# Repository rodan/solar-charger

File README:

12v lead-acid battery charger for 15-36V photovoltaic cells

 UNDER DEVELOPMENT

 source:       https://github.com/rodan/solar-charger 
 author:       Petre Rodan <2b4eda@subdimension.ro>
 license:      GNU GPLv3
 toolchain used: msp430-elf-gcc (Mitto Systems Limited - msp430-gcc 9.2.0.50) 9.2.0 linux

Features:
 - an MSP430F5510 uC controls all aspects of charging a 12v Pb battery
 - programming either via spy-bi-wire or usb (untested)
 - logging capability to a uSd card
 - backup 3v Li cell for keeping the RTC up-to-date
 - analog readout of battery voltage, input voltage, charge current, thermistor temperature, internal temperature
 - possibility to stop the charge if a condition is met
 - 8 status leds for verbose blinkiness
 - very low quiescent current

rev1 - used a LandStar charge controller that got replaced in rev3 with a PB137ACV ic
rev3 - 3V Li cell acts as bakup power for the uC, an SDcard is provided for logging
rev4 - SDcard is removed, 3V Li cell replaced by a 3.7v lipo + charging circuitry

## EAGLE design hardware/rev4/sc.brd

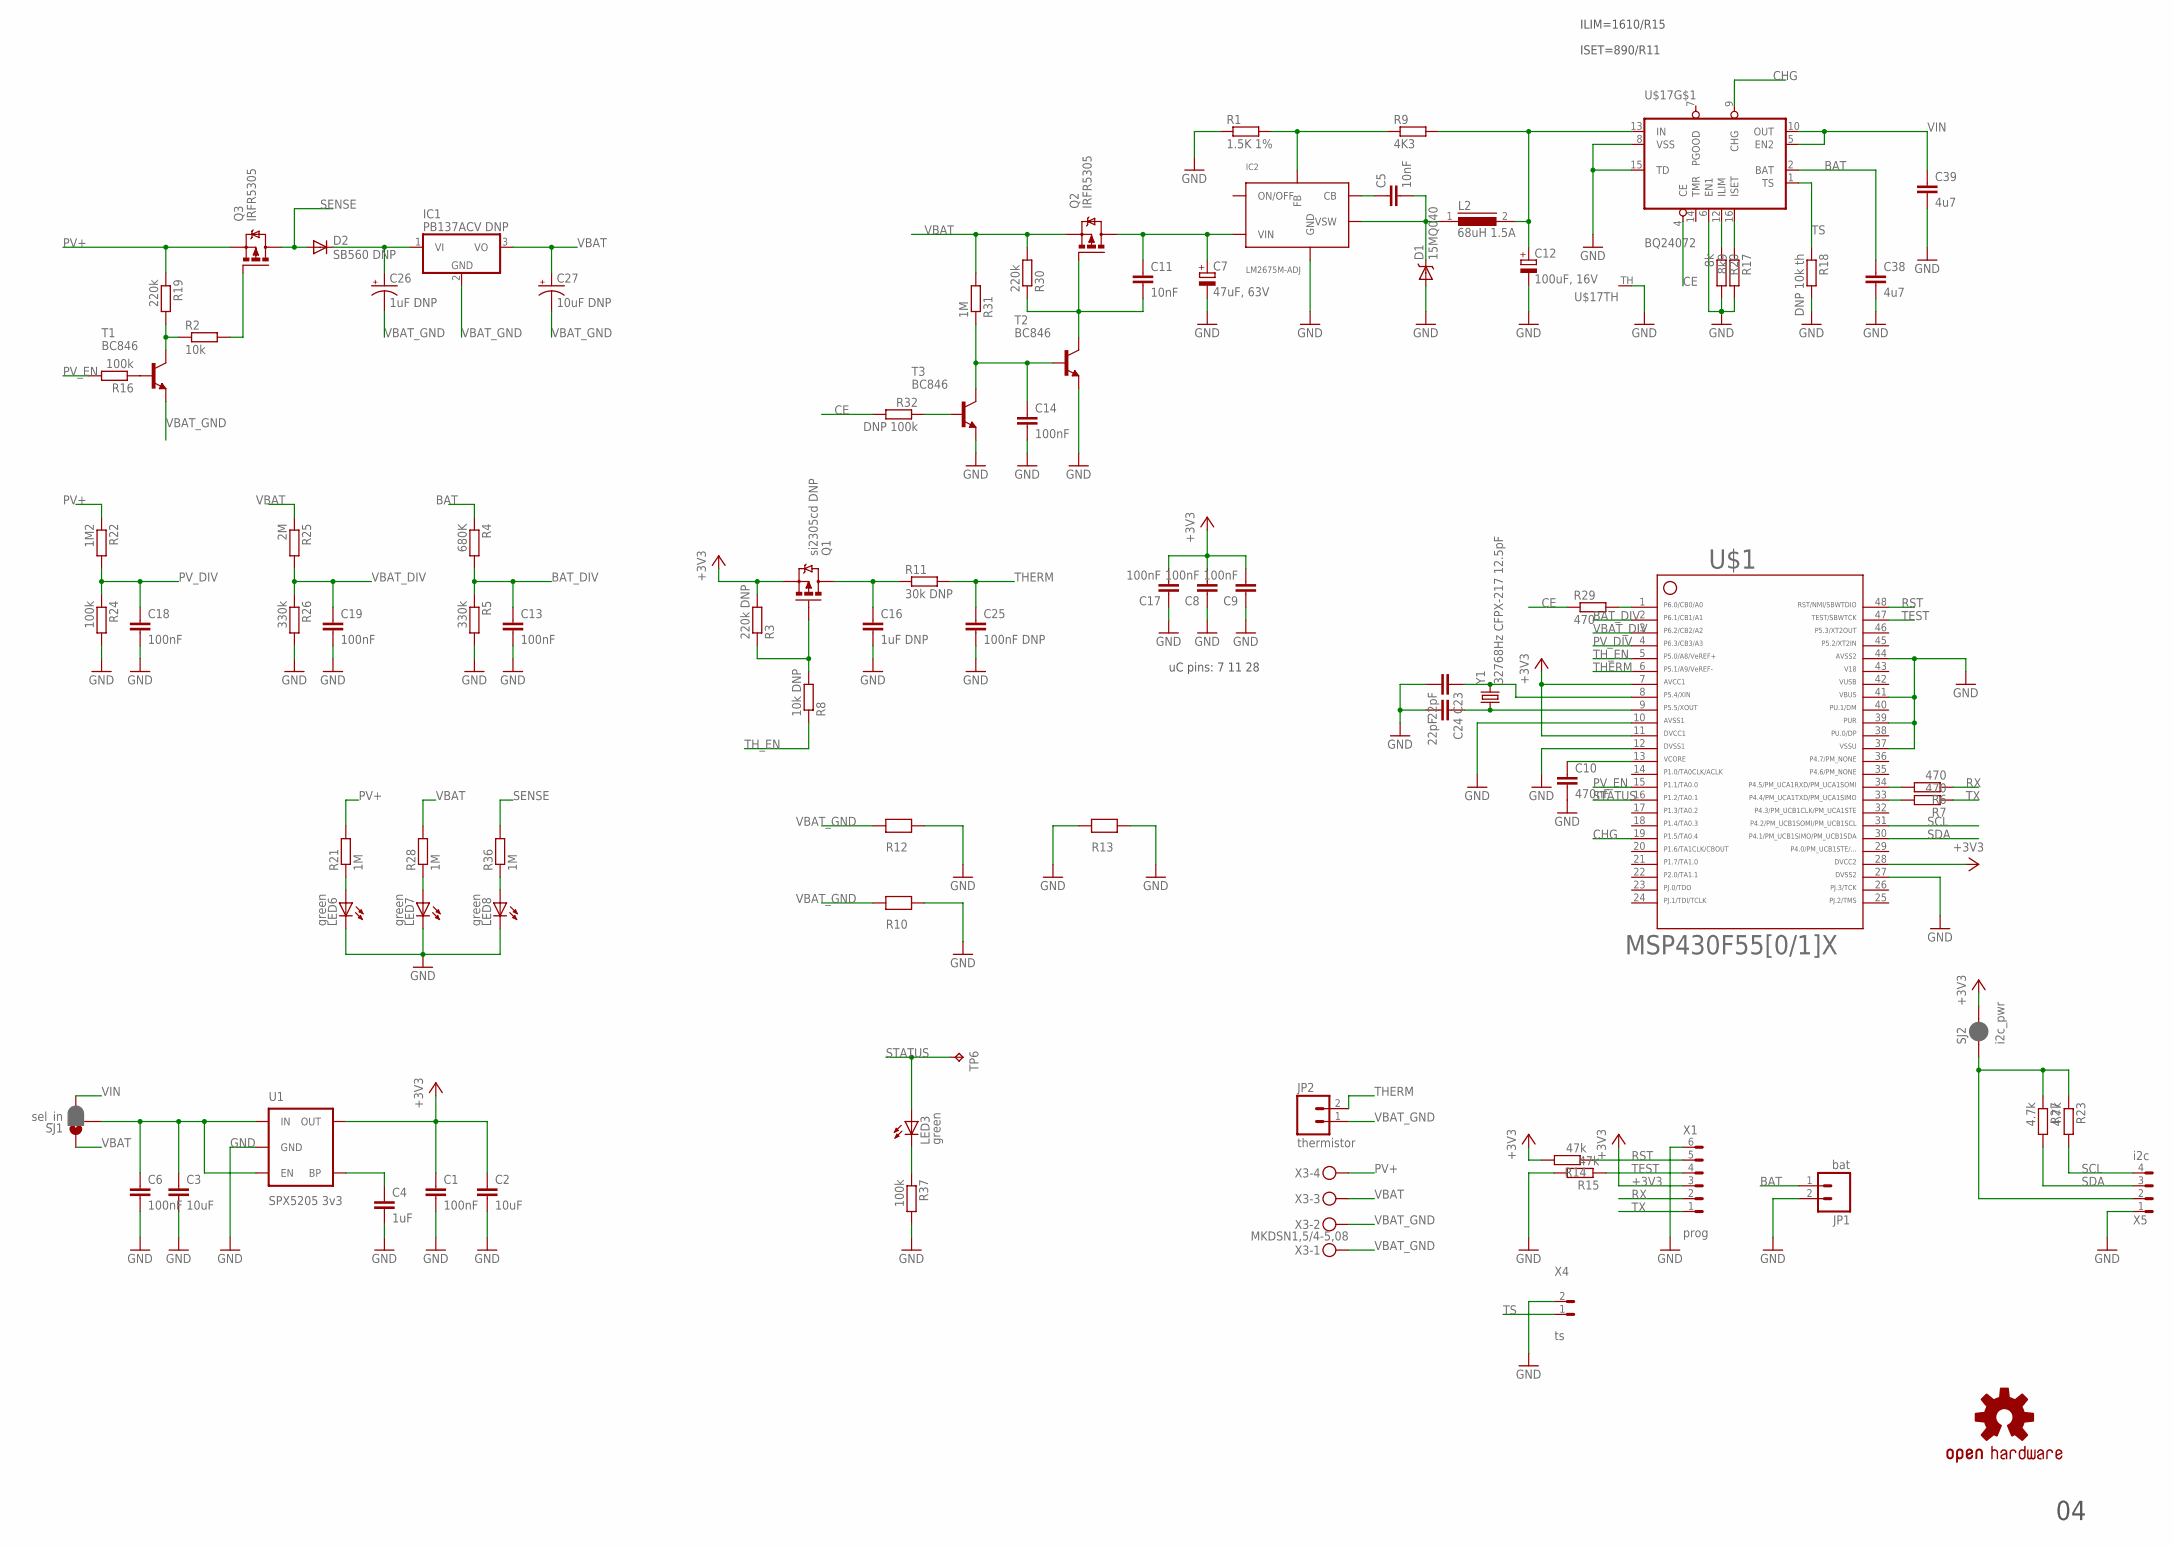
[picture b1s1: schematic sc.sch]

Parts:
C1, C6, C8, C9, C13, C14, C17, C18, C19: 100nF; C0805
C2, C3: 10uF; C1206
C4: 1uF; C0805
C5, C11: 10nF; C0805
C7: 47uF, 63V; PANASONIC_F
C10: 470nF; C0805
C12: 100uF, 16V; PANASONIC_D
C16: 1uF DNP; C0805
C23, C24: 22pF; C0805
C25: 100nF DNP; C0805
C26: 1uF DNP; PANASONIC_D
C27: 10uF DNP; PANASONIC_D
C38, C39: 4u7; C1206
D1: 15MQ040; SMA-DIODE
D2: SB560 DNP; C1702-05
IC1: PB137ACV DNP; TO220V
IC2: LM2675M-ADJ; SO-08
JP1: bat; 1X02
JP2: thermistor; 1X02
L2: 68uH 1.5A; DR125
LED3: green; CHIPLED_0805
LED6, LED7, LED8: green; CHIP-LED0805
Q1: si2305cd DNP; SOT23-3_POWER@1
Q2, Q3: IRFR5305; D-PAK_TO252AA
R1: 1.5K 1%; R0805W
R2: 10k; R0805W
R3: 220k DNP; R0805W
R4: 680K; R0805W
R5, R26: 330k; R0805W
R6, R7, R29: 470; R0805W
R8: 10k DNP; R0805W
R9: 4K3; R0805W
R10, R12, R13: 0R_0805; R0805W
R11: 30k DNP; R0805W
R14, R15: 47k; R0805W
R16, R24, R37: 100k; R0805W
R17: 8k9; R0805W
R18: DNP 10k th; R0805W
R19, R30: 220k; R0805W
R20: 8k; R0805W
R21, R28, R31, R36: 1M; R0805W
R22: 1M2; R0805W
R23, R27: 4.7k; R0805W
R25: 2M; R0805W
R32: DNP 100k; R0805W
SJ1: sel_in; PAD-JUMPER-3-2OF3_NC_BY_PASTE_YES_SILK_FULL_BOX
SJ2: i2c_pwr; PAD-JUMPER-2-NC_BY_PASTE_YES_SILK
T1, T2, T3: BC846; SOT23
TP6: TPTP12R; TP12R
U1: SPX5205 3v3; SOT23-5
U$1: F55[0/1]X---PT48; PT48
U$7: OSHW-LOGOM; OSHW-LOGO-M
U$17: BQ24072; S-PVQFN-N16
X1: prog; 0530480610
X3: MKDSN1,5/4-5,08
X4: ts; 0530480210
X5: i2c; 0530480401
Y1: 32768Hz CFPX-217 12.5pF; CRYSTAL-SMD-3.2X1.5

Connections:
42: U$1.42
43: U$1.43
46: U$1.46
+3V3: C1.1, C2.1, C8.2, C9.2, C17.2, Q1.2 (S), R3.2, R14.2, SJ2.2, U1.5 (OUT), U$1.7, U$1.11, U$1.28, X1.3 (4)
BAT: C38.1, JP1.1, R4.1, U$17.2 (BAT)
BAT_DIV: C13.1, R4.2, R5.1, U$1.2
CE: R29.1, R32.2, U$17.4 (CE)
CHG: U$1.19, U$17.9 (CHG)
GND: C1.2, C2.2, C3.2, C4.2, C6.2, C7.-, C8.1, C9.1, C10.2, C12.-, C13.2, C14.2, C16.2, C17.1, C18.2, C19.2, C23.2, C24.2, C25.2, C38.2, C39.2, D1.A, IC2.6 (GND), JP1.2, LED6.C, LED7.C, LED8.C, R1.1, R5.2, R10.2, R12.2, R13.1, R13.2, R15.2, R17.2, R18.2, R20.2, R24.2, R26.2, R37.2, T2.2 (E), T3.2 (E), U1.2 (GND), U$1.10, U$1.12, U$1.27, U$1.37, U$1.39, U$1.41, U$1.44, U$17.6 (EN1), U$17.8 (VSS), U$17.15 (TD), U$17.TH, X1.6 (1), X4.2 (1), X5.1 (4)
unnamed: C16.1, Q1.3 (D), R11.1
unnamed: C4.1, U1.4 (BP)
unnamed: R16.1, T1.1 (B)
unnamed: IC2.4 (FB), R1.2, R9.1
unnamed: R2.1, R19.2, T1.3 (C)
unnamed: C10.1, U$1.13
unnamed: C3.1, C6.1, SJ1.2, U1.1 (IN), U1.3 (EN)
unnamed: C26.+, D2.C, IC1.1 (VI)
unnamed: C5.2, D1.C, IC2.8 (VSW), L2.1
unnamed: C5.1, IC2.1 (CB)
unnamed: R6.2, U$1.34
unnamed: LED6.A, R21.1
unnamed: R7.2, U$1.33
unnamed: Q1.1 (G), R3.1, R8.2
unnamed: C12.+, L2.2, R9.2, U$17.13 (IN)
unnamed: C11.2, Q2.1 (G), R30.1, T2.3 (C)
unnamed: R23.1, R27.1, SJ2.1, X5.2 (3)
unnamed: LED7.A, R28.1
unnamed: R29.2, U$1.1
unnamed: C14.1, R31.1, T2.1 (B), T3.3 (C)
unnamed: R32.1, T3.1 (B)
unnamed: LED8.A, R36.1
unnamed: C24.1, U$1.9, Y1.P$1 (1)
unnamed: C23.1, U$1.8, Y1.P$2 (2)
unnamed: Q3.1 (G), R2.2
unnamed: R17.1, U$17.16 (ISET)
unnamed: R20.1, U$17.12 (ILIM)
unnamed: LED3.C, R37.1
unnamed: C7.+, C11.1, IC2.7 (VIN), Q2.4 (D)
PV+: Q3.3 (S), R19.1, R21.2, R22.1, X3.4
PV_DIV: C18.1, R22.2, R24.1, U$1.4
PV_EN: R16.2, U$1.15
RST: R14.1, U$1.48, X1.5 (2)
RX: R6.1, X1.2 (5)
SCL: R23.2, U$1.31, X5.4 (1)
SDA: R27.2, U$1.30, X5.3 (2)
SENSE: D2.A, Q3.4 (D), R36.2
STATUS: LED3.A, TP6.TP, U$1.16
TEST: R15.1, U$1.47, X1.4 (3)
THERM: C25.1, JP2.2, R11.2, U$1.6
TH_EN: R8.1, U$1.5
TS: R18.1, U$17.1 (TS), X4.1 (2)
TX: R7.1, X1.1 (6)
VBAT: C27.+, IC1.3 (VO), Q2.3 (S), R25.1, R28.2, R30.2, R31.2, SJ1.1, X3.3
VBAT_DIV: C19.1, R25.2, R26.1, U$1.3
VBAT_GND: C26.-, C27.-, IC1.2 (GND), JP2.1, R10.1, R12.1, T1.2 (E), X3.1, X3.2
VIN: C39.1, SJ1.3, U$17.5 (EN2), U$17.10 (OUT)

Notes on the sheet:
uC pins: 7 11 28
ILIM=1610/R15
ISET=890/R11

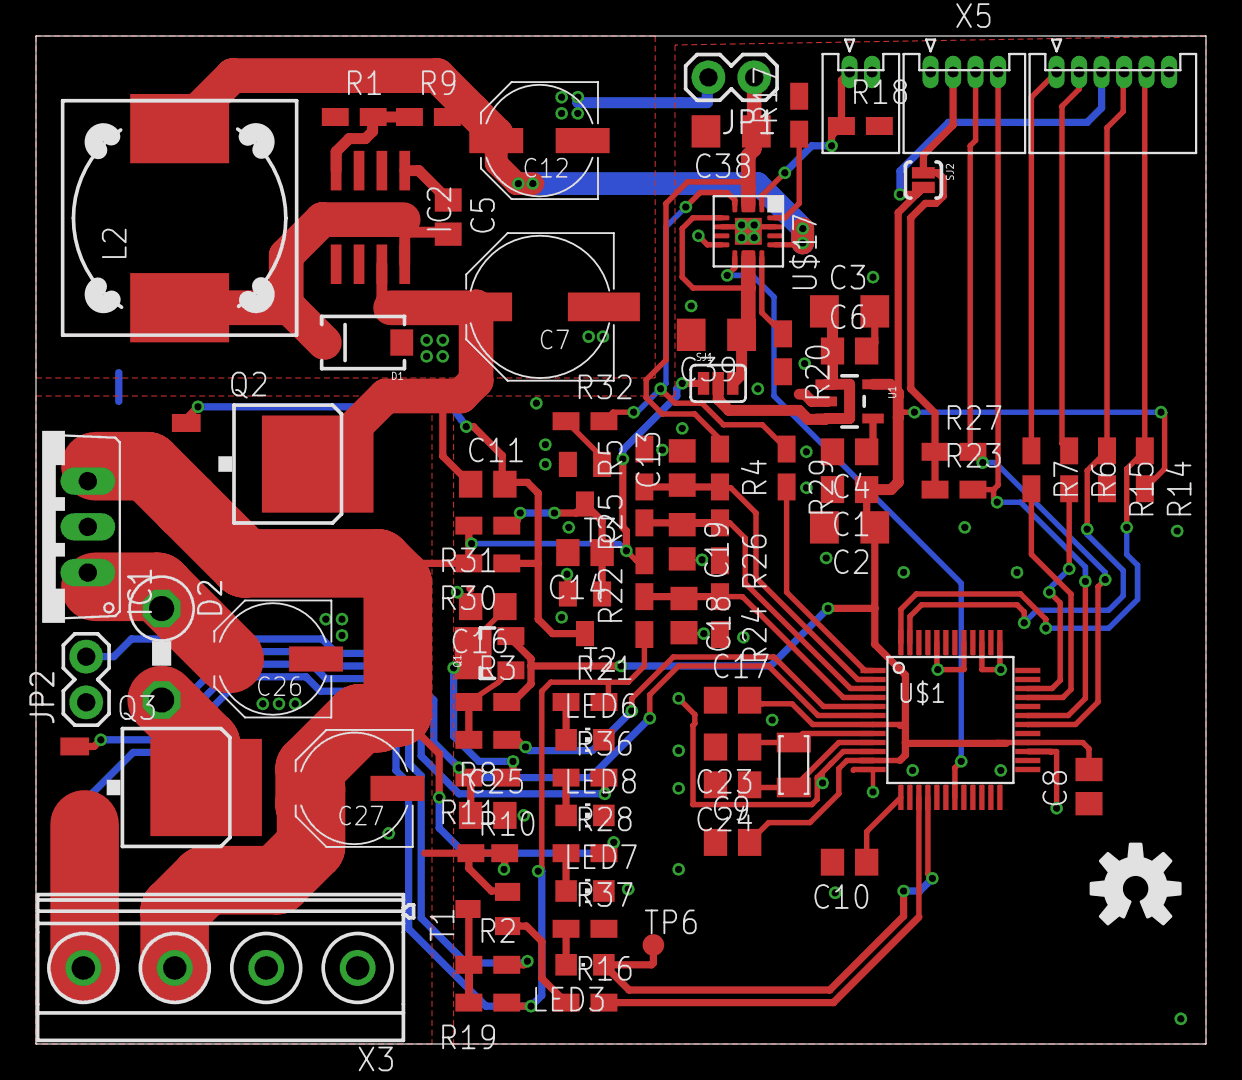
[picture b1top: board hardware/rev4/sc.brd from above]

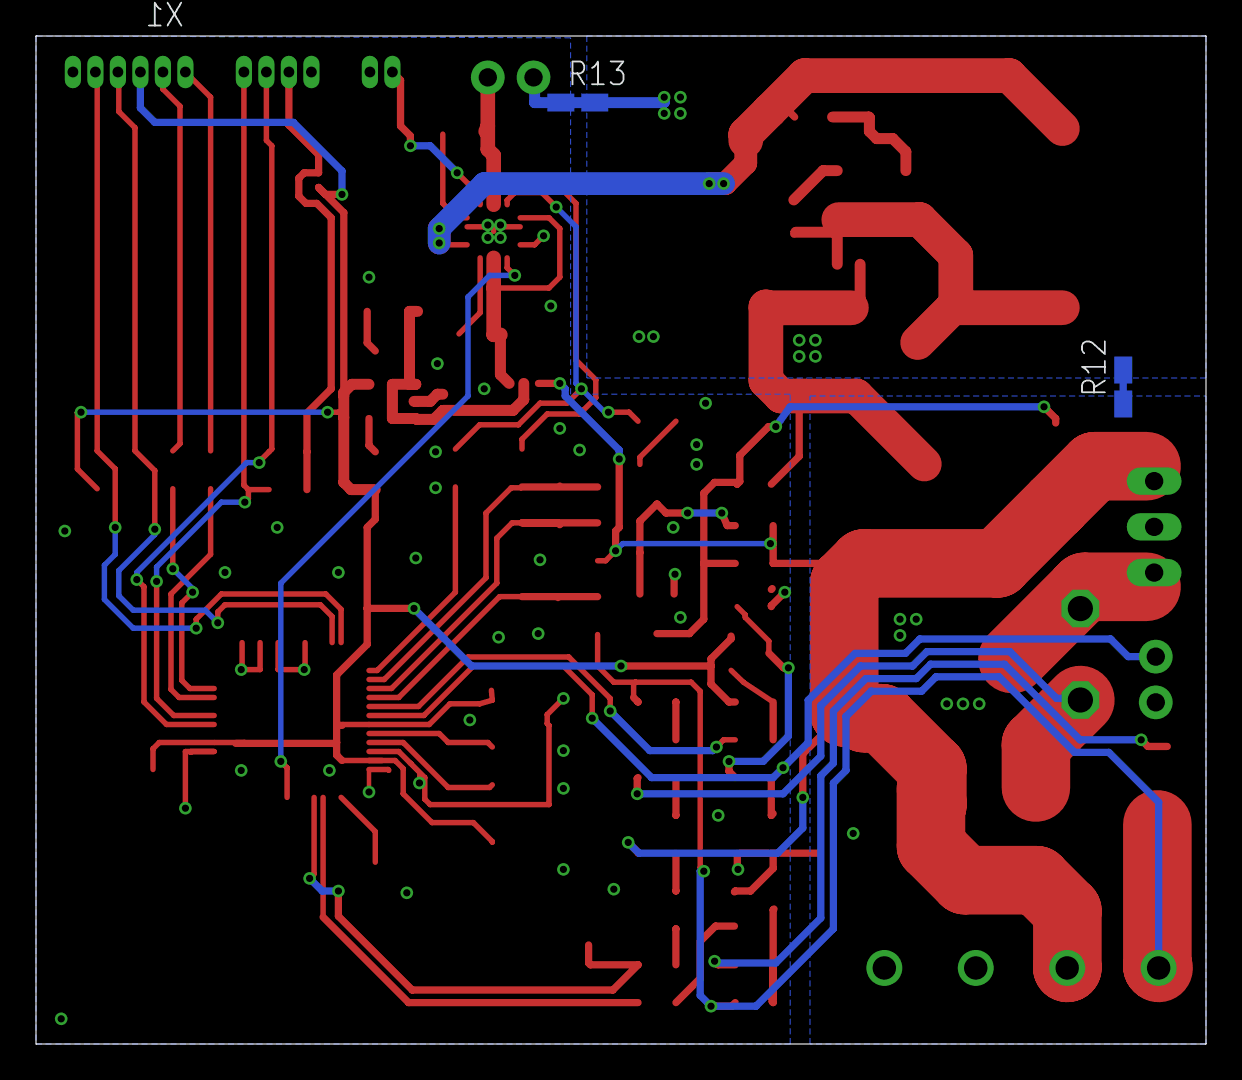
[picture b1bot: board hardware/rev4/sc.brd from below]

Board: 2 copper layers, 65.0 x 56.0 mm, 88 parts (2 on the bottom side), 53 nets.

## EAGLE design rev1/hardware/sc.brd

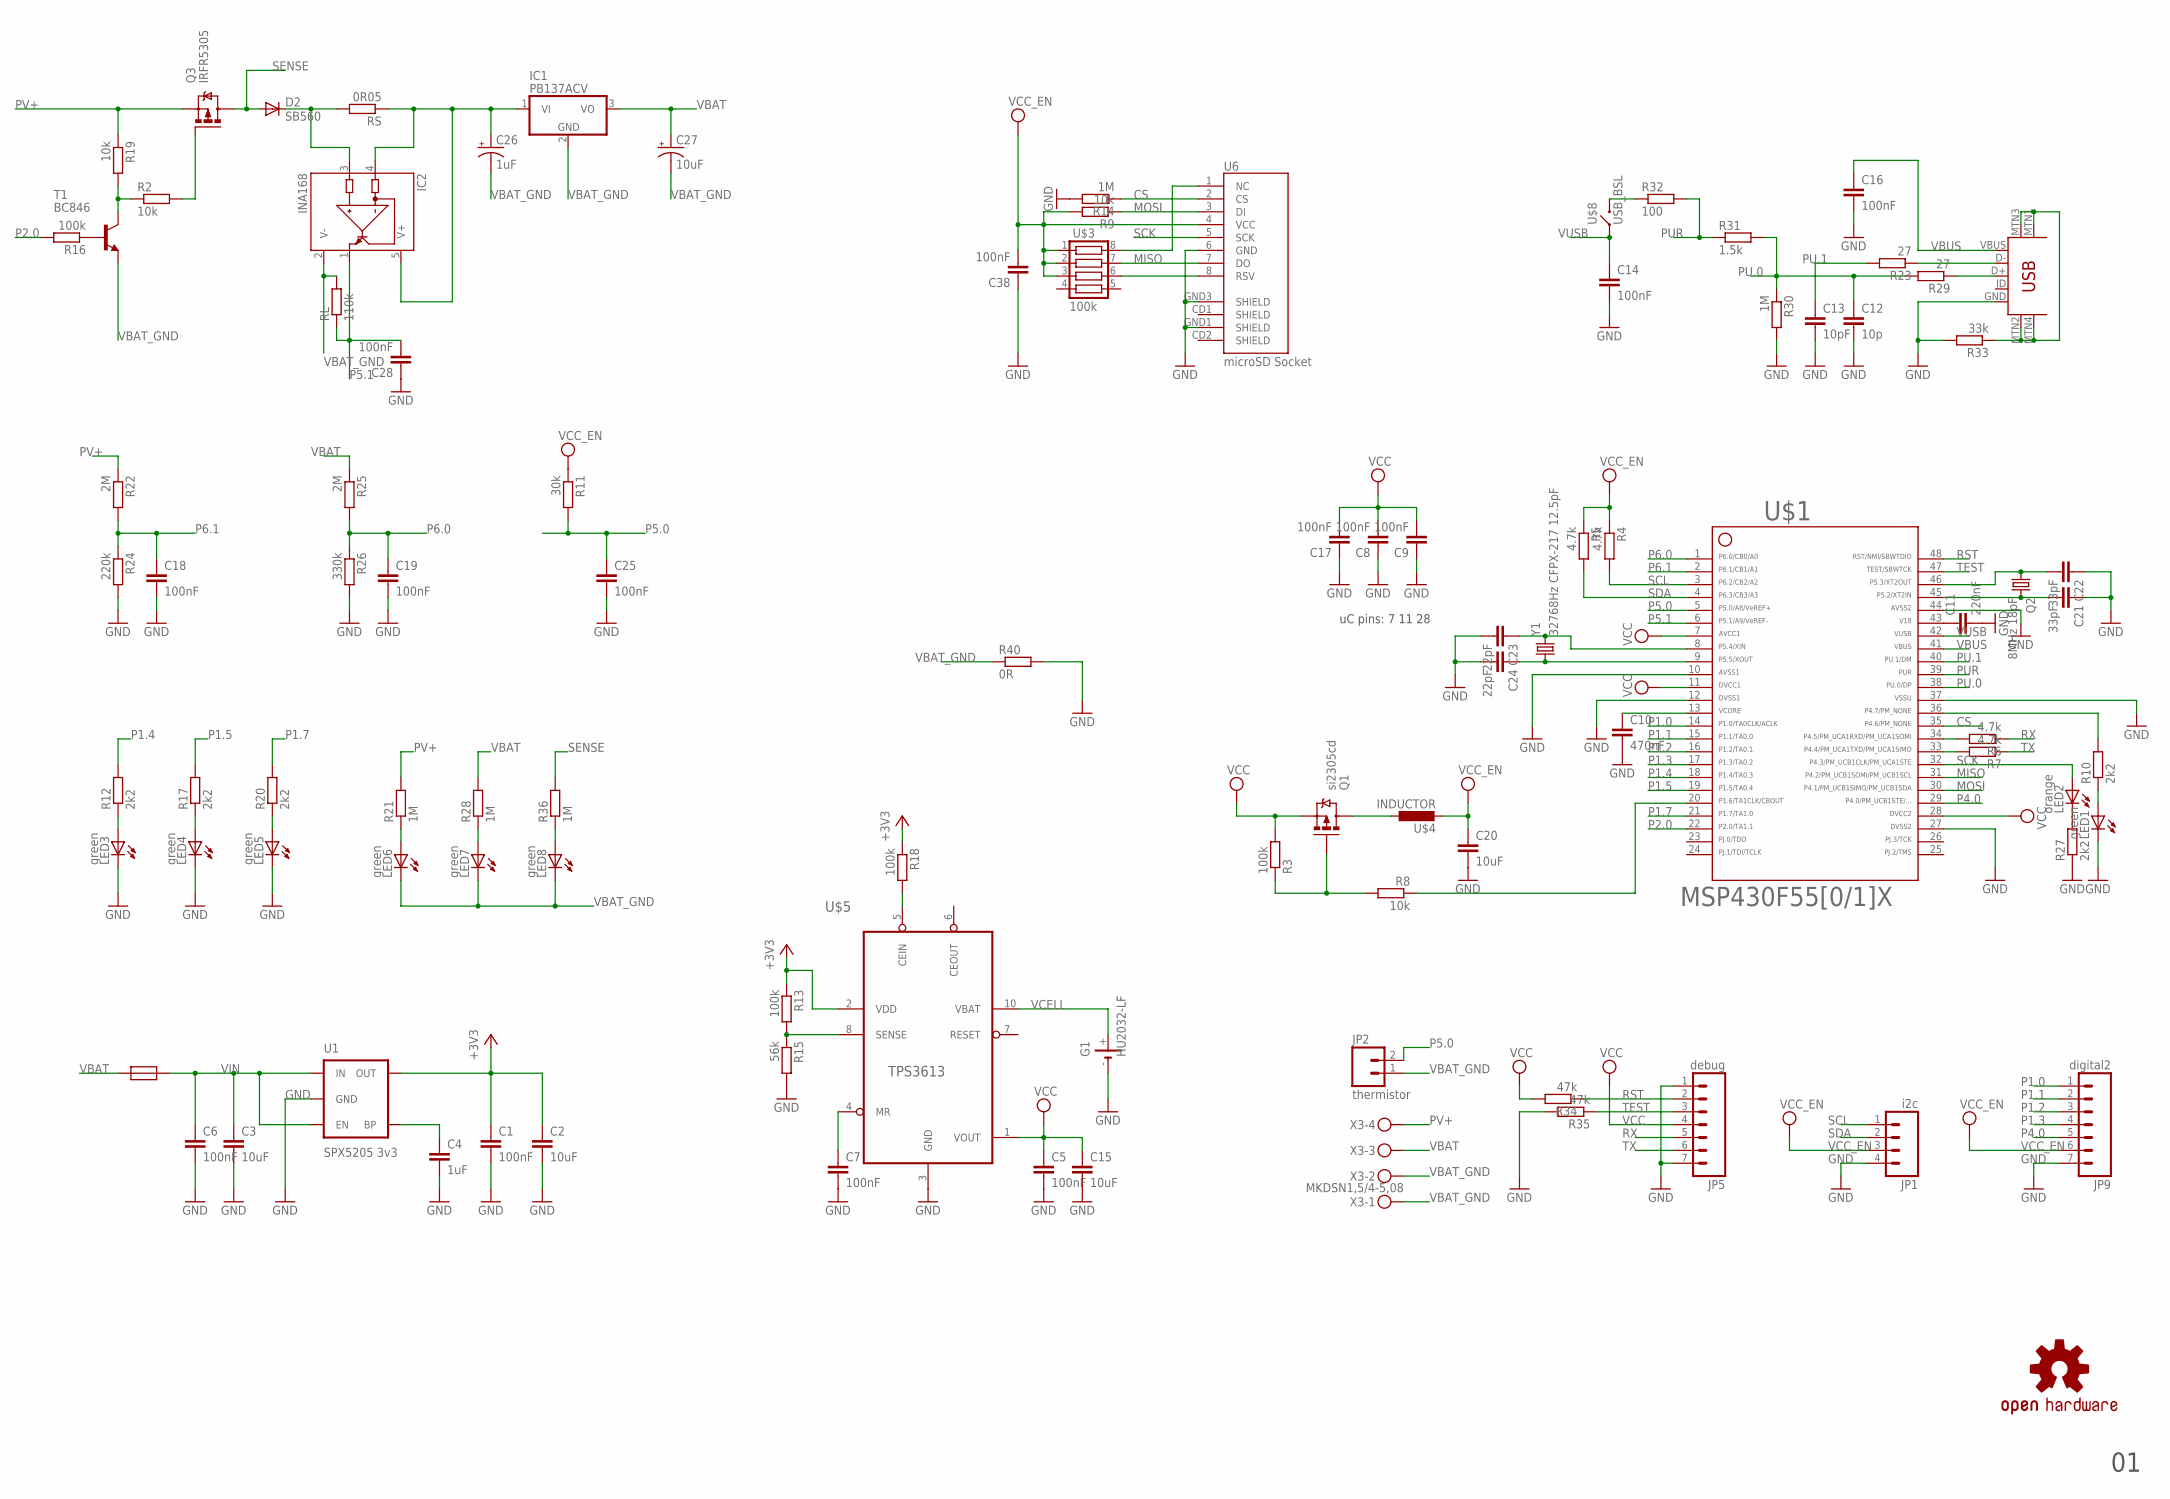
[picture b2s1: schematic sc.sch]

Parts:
C1, C5, C6, C7, C8, C9, C14, C16, C17, C18, C19, C25, C28, C38: 100nF; C0805
C2, C3, C15, C20: 10uF; C1206
C4: 1uF; C0805
C10: 470nF; C0805
C11: 220nF; C0805
C12: 10p; C0805
C13: 10pF; C0805
C21, C22: 33pF; C0805
C23, C24: 22pF; C0805
C26: 1uF; PANASONIC_D
C27: 10uF; PANASONIC_D
D2: SB560; C1702-05
G1: HU2032-LF
IC1: PB137ACV; TO220V
IC2: INA168; SOT23-5
JP1: i2c; 1X04
JP2: thermistor; 1X02
JP5: debug; 1X07
JP9: digital2; 1X07
LED1, LED3, LED4, LED5, LED6, LED7, LED8: green; CHIP-LED0805
LED2: orange; CHIP-LED0805
Q1: si2305cd; SOT23-3_POWER
Q2: 8MHz 18pF; CRYSTAL_5X3.2
Q3: IRFR5305; D-PAK_TO252AA
R2, R8, R9, R19: 10k; R0805W
R3, R13, R16, R18: 100k; R0805W
R4, R5, R6, R7: 4.7k; R0805W
R10, R12, R17, R20, R27: 2k2; R0805W
R11: 30k; R0805W
R14, R21, R28, R30, R36: 1M; R0805W
R15: 56k; R0805W
R22, R25: 2M; R0805W
R23, R29: 27; R0805W
R24: 220k; R0805W
R26: 330k; R0805W
R31: 1.5k; R0805W
R32: 100; R0805W
R33: 33k; R0805W
R34, R35: 47k; R0805W
R40: 0R; R0805W
RL: 110k; R0805W
RS: 0R05; TO220ACS
T1: BC846; SOT23
U1: SPX5205 3v3; SOT23-5
U6: microSD Socket; MICRO-SD-SOCKET-PP
U$1: F55[0/1]X---PT48; PT48
U$2: RESETTABLE; 1210
U$3: 100k; YC164
U$4: INDUCTOR; L0805W
U$5: TPS3613; MSOP_10P
U$6: USB-MINIB-5PIN; USB-MINIB
U$7: OSHW-LOGOM; OSHW-LOGO-M
U$8: USB_BSL; 6X3.5_TACTILE_SW
X3: MKDSN1,5/4-5,08
Y1: 32768Hz CFPX-217 12.5pF; CRYSTAL-SMD-3.2X1.5

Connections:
+3V3: C1.1, C2.1, R13.1, R18.1, U1.5 (OUT), U$5.2 (VDD)
CS: R14.1, U6.2 (CS), U$1.35
EN: R8.1, U$1.20
GND: C1.2, C2.2, C3.2, C4.2, C5.2, C6.2, C7.2, C8.1, C9.1, C10.2, C11.2, C12.2, C13.2, C14.2, C15.2, C16.2, C17.1, C18.2, C19.2, C20.2, C21.1, C22.1, C23.2, C24.2, C25.2, C28.1, C38.1, G1.-, JP1.4, JP5.1, JP5.7, JP9.7, LED1.C, LED3.C, LED4.C, LED5.C, R14.2, R15.2, R24.2, R26.2, R27.1, R30.2, R33.2, R35.2, R40.2, U1.2 (GND), U6.6 (GND), U6.GND1 (SHIELD), U6.GND3 (SHIELD), U$1.10, U$1.12, U$1.27, U$1.37, U$1.44, U$5.3 (GND), U$6.GND
LED: R10.2, U$1.36
MISO: U6.7 (DO), U$1.31, U$3.7
MOSI: R9.1, U6.3 (DI), U$1.30
unnamed: LED1.A, R10.1
unnamed: C4.1, U1.4 (BP)
unnamed: R16.1, T1.1 (B)
unnamed: U6.1 (NC), U$3.8
unnamed: R2.1, R19.2, T1.3 (C)
unnamed: C10.1, U$1.13
unnamed: C11.1, U$1.43
unnamed: LED3.A, R12.1
unnamed: C26.+, IC1.1 (VI), IC2.4 (IN-), IC2.5 (V+), RS.A (1)
unnamed: R6.2, U$1.34
unnamed: LED6.A, R21.1
unnamed: R7.2, U$1.33
unnamed: Q1.1 (G), R3.1, R8.2
unnamed: LED4.A, R17.1
unnamed: LED5.A, R20.1
unnamed: C22.2, Q2.P$1 (1), U$1.46
unnamed: LED7.A, R28.1
unnamed: R13.2, R15.1, U$5.8 (SENSE)
unnamed: C7.1, U$5.4 (MR)
unnamed: R18.2, U$5.5 (CEIN)
unnamed: R29.1, U$6.D+
unnamed: C21.2, Q2.P$2 (2), U$1.45
unnamed: LED8.A, R36.1
unnamed: C24.1, U$1.9, Y1.P$1 (1)
unnamed: C23.1, U$1.8, Y1.P$2 (2)
unnamed: U6.8 (RSV), U$3.6
unnamed: Q3.1 (G), R2.2
unnamed: R23.1, U$6.D-
unnamed: D2.C, IC2.3 (IN+), RS.C (2)
unnamed: R32.1, U$8.2
unnamed: R33.1, U$6.MTN1 (MTN2), U$6.MTN2 (MTN3), U$6.MTN3 (MTN1), U$6.MTN4
unnamed: Q1.3 (D), U$4.1
unnamed: LED2.C, R27.2
P1.0: JP9.1, U$1.14
P1.1: JP9.2, U$1.15
P1.2: JP9.3, U$1.16
P1.3: JP9.4, U$1.17
P1.4: R12.2, U$1.18
P1.5: R17.2, U$1.19
P1.7: R20.2, U$1.21
P2.0: R16.2, U$1.22
P4.0: JP9.5, U$1.29
P5.0: C25.1, JP2.2, R11.2, U$1.5
P5.1: C28.2, IC2.1 (OUT), RL.1, U$1.6
P6.0: C19.1, R25.2, R26.1, U$1.1
P6.1: C18.1, R22.2, R24.1, U$1.2
PU.0: C12.1, R29.2, R30.1, R31.2, U$1.38
PU.1: C13.1, R23.2, U$1.40
PUR: R31.1, R32.2, U$1.39
PV+: Q3.3 (S), R19.1, R21.2, R22.1, X3.4
RST: JP5.2, R34.1, U$1.48
RX: JP5.5, R6.1
SCK: LED2.A, U6.5 (SCK), U$1.32
SCL: JP1.1, R4.2, U$1.3
SDA: JP1.2, R5.2, U$1.4
SENSE: D2.A, Q3.4 (D), R36.2
TEST: JP5.3, R35.1, U$1.47
TX: JP5.6, R7.1
VBAT: C27.+, IC1.3 (VO), R25.1, R28.2, U$2.P$1, X3.3
VBAT_GND: C26.-, C27.-, IC1.2 (GND), IC2.2 (V-), JP2.1, LED6.C, LED7.C, LED8.C, R40.1, RL.2, T1.2 (E), X3.1, X3.2
VBUS: C16.1, U$1.41, U$6.VBUS
VCC: C5.1, C8.2, C9.2, C15.1, C17.2, JP5.4, Q1.2 (S), R3.2, R34.2, U$1.7, U$1.11, U$1.28, U$5.1 (VOUT)
VCC_EN: C20.1, C38.2, JP1.3, JP9.6, R4.1, R5.1, R9.2, R11.1, U6.4 (VCC), U$3.1, U$3.2, U$3.3, U$4.2
VCELL: G1.+, U$5.10 (VBAT)
VIN: C3.1, C6.1, U1.1 (IN), U1.3 (EN), U$2.P$2
VUSB: C14.1, U$1.42, U$8.1

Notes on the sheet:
uC pins: 7 11 28

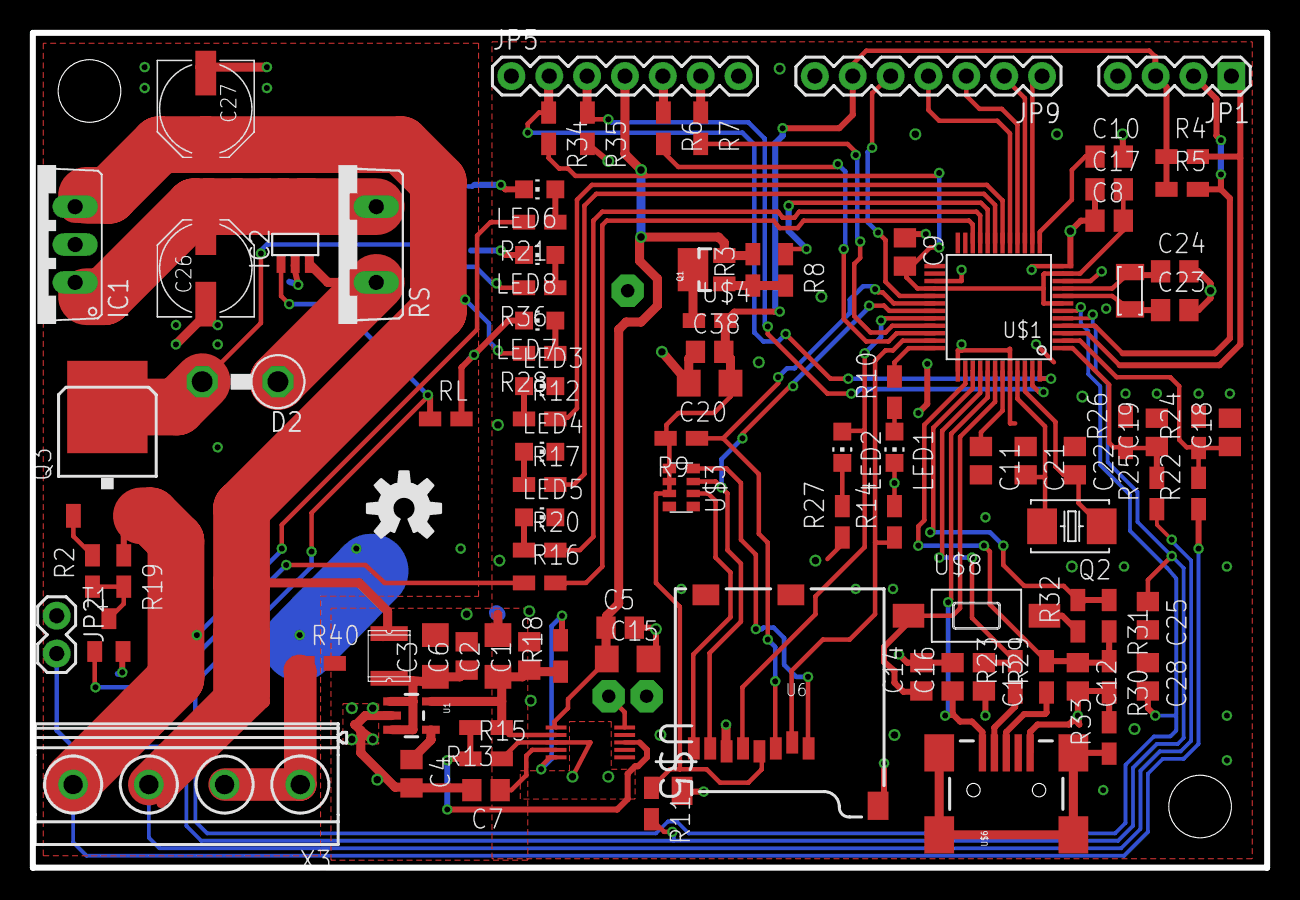
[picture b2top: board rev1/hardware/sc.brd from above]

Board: 2 copper layers, 82.8 x 56.0 mm, 99 parts (1 on the bottom side), 73 nets.

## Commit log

2013-06-08 calculate resistor dividers and XT1, XT2 load caps
2013-06-08 add firmware
2013-06-10 relay tests
2013-06-11 ADC is working. WEEEEEE!
2013-06-17 100uA reached
2013-06-17 add watchdog
2013-06-17 enable daylight saving time module
2013-06-17 less code when coin cell power is used
2013-06-18 add ADC calibration mode
2013-06-20 add debug info
2013-07-28 use different p-mosfet
2013-07-28 save status to sd-card only if relays activate
2013-09-14 rev3
2013-10-13 make LandStar optional. pb137 is the default
2013-10-24 review part values
2013-10-26 resistor tweaks
2013-10-26 resistor value tweaks
2013-10-26 switch to hardware rev 03
2013-10-27 calibrations
2013-10-27 lower LED power
2013-10-27 int temp calibration
2013-10-28 cleanup
2013-10-29 keep track of programming time
2013-11-23 add charging info
2013-11-24 fix ADC REFVSEL bug
2013-11-24 use reference libs
2013-11-25 switched to FatFs R0.10
2013-11-25 fix charge_enabled graph
2013-11-28 allow negative temperatures
2014-01-27 remove python scripts
2015-10-26 add rev2
2015-10-27 rev2 routing 2/3
2015-11-01 board ready
2015-11-10 fw rev2
2021-05-21 rev4
2021-05-21 rewritten parts of the rev4 code to compile with gcc 9.2.0
2021-05-21 add static scan
2021-05-22 rev3 changes for 9.2.0 gcc
2021-08-01 control pins working
2021-08-15 adc, rtc work
2021-08-16 timer_a2 and scheduling
2021-08-16 testing stage
2021-08-17 pwr_mng_check_pv() rescheduling
2021-08-17 latest
2021-08-17 add README files
2021-11-05 Makefile update for latest reference-lib version
2021-11-11 changes needed by the latest reflib
2021-11-29 library name change
2021-12-02 clock_pin_init() is mandatory in new atlas
2022-01-09 changes needed by latest HAL lib
2022-01-12 uart interface changes needed by latest atlas430

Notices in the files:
parts and their libraries:
SparkFun-Capacitors: Licensing: CC v3.0 Share-Alike You are welcome to use this library for commercial purposes.
SparkFun-DiscreteSemi: Licensing: Creative Commons ShareAlike 4.0 International - https://creativecommons.org/licenses/by-sa/4.0
